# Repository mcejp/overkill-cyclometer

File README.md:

# Overkill Cyclocomputer

## Compile it

### For Pi Pico

Prerequisites:
- Raspberry Pi Pico SDK
- Recent arm-none-eabi-gcc toolchain
- ImageMagick (`convert` tool) & xxd

```
mkdir build
cd build
env PICO_SDK_PATH=... PICO_TOOLCHAIN_PATH=... cmake ..
make

# flash
cp bikECU.uf2 /media/RPI-RP2/
```

### For PC (Simulation)

Prerequisites:
- C++20 compiler
- Libretro frontent ([SDLArch](https://github.com/heuripedes/sdlarch) / [RetroArch](https://www.retroarch.com/))
- ImageMagick (`convert` tool) & xxd

```
mkdir build_libretro
cd build_libretro
cmake ..
make
sdlarch ./libbikECU_libretro.so
# alternatively:
# retroarch -L ./libbikECU_libretro.so
```

## Credits

- curses_vector fonts: http://www.bay12forums.com/smf/index.php?topic=161328.0
- libretro: Copyright (C) 2010-2020 The RetroArch team
- [SeeedGrayOLED library](https://github.com/Seeed-Studio/OLED_Display_96X96): Copyright (c) 2011 seeed technology inc.

## BOM

TBD

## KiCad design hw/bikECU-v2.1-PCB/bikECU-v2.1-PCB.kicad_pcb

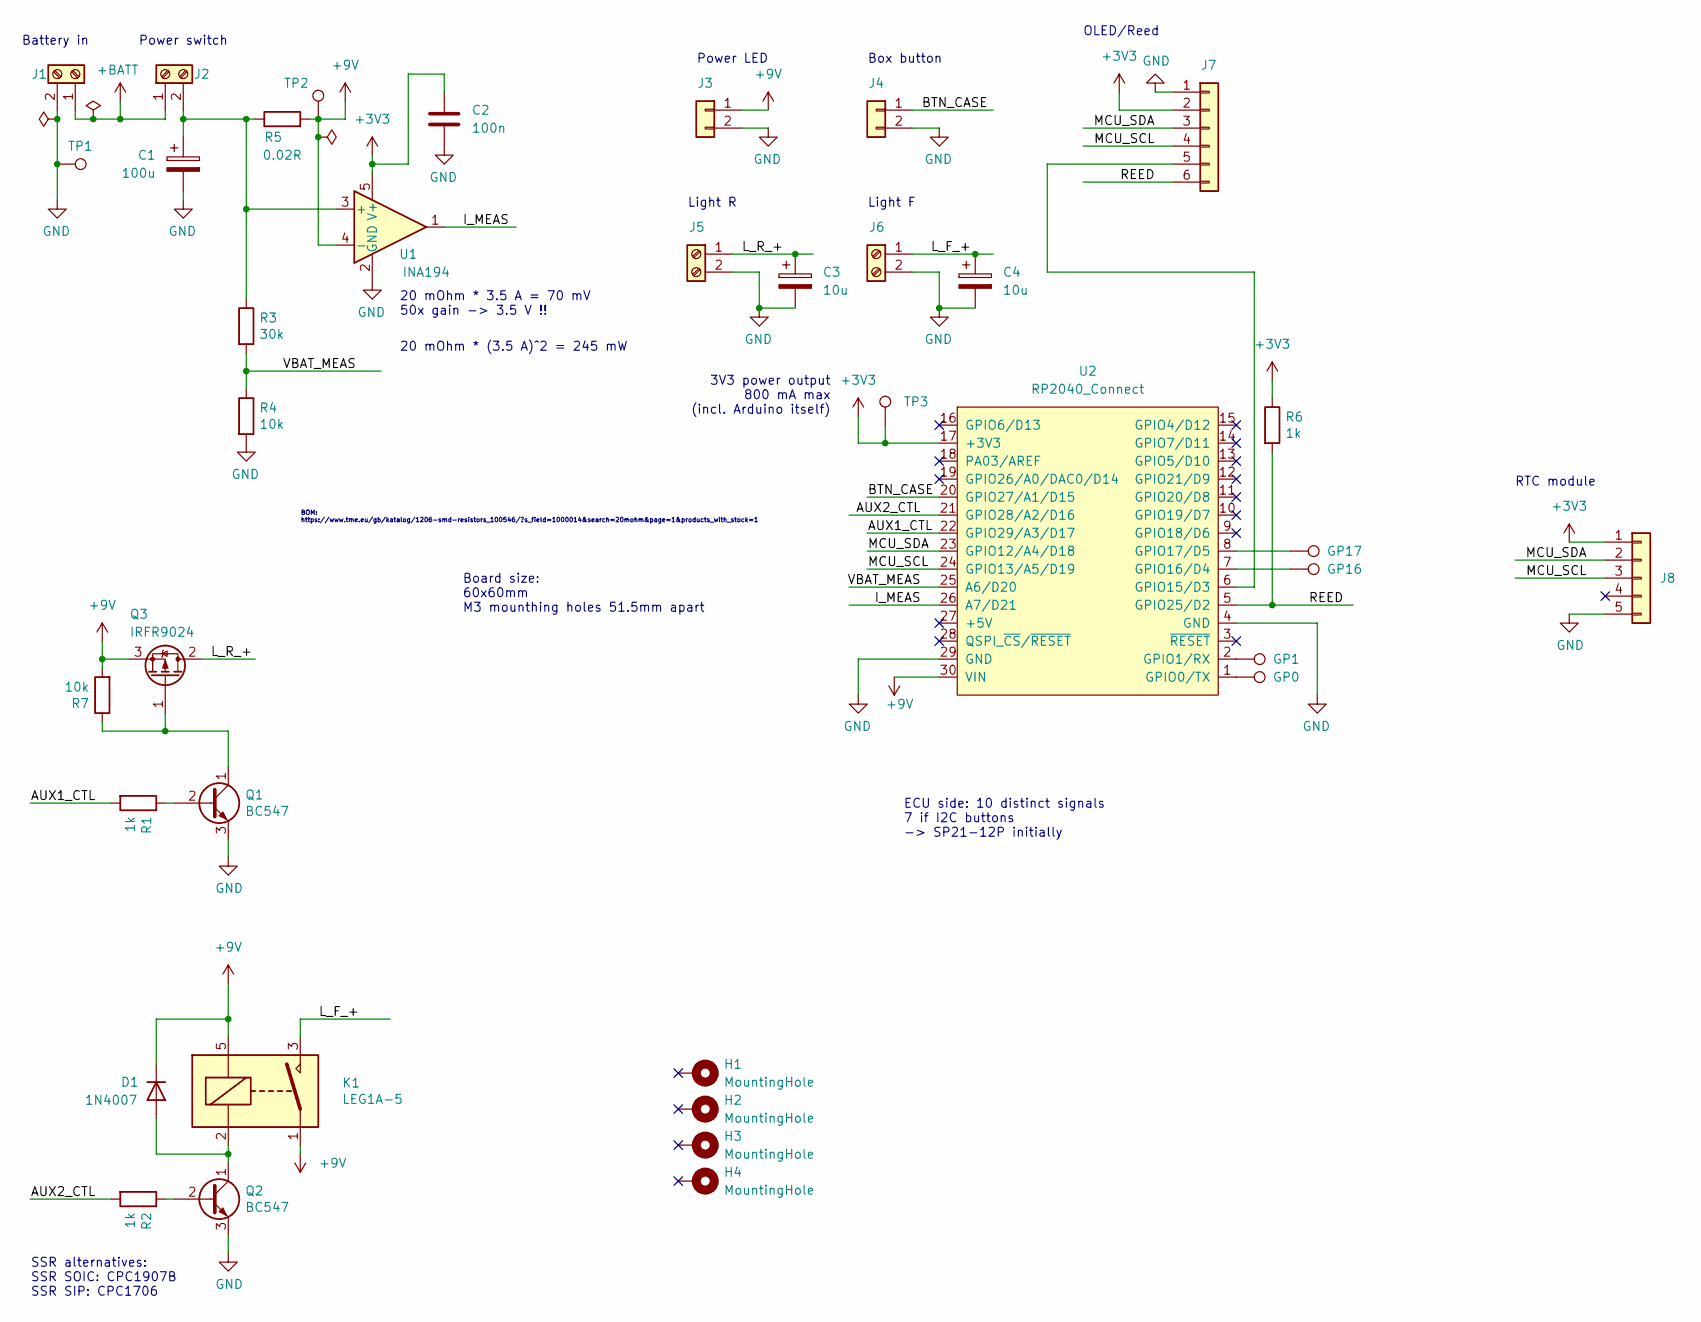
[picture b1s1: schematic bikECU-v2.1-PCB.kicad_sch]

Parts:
C1: 100u; CP_Radial_D6.3mm_P2.50mm
C2: 100n; C_0805_2012Metric_Pad1.18x1.45mm_HandSolder
C3, C4: 10u; CP_Radial_D5.0mm_P2.00mm
D1: 1N4007; D_DO-41_SOD81_P10.16mm_Horizontal
GP0, GP1, GP16, GP17: TestPoint; TestPoint_THTPad_D2.0mm_Drill1.0mm
H1, H2, H3, H4: MountingHole; MountingHole_3.2mm_M3_Pad
J1: Power_in; TerminalBlock_TE_282834-2_1x02_P2.54mm_Horizontal
J2: Power_sw; TerminalBlock_TE_282834-2_1x02_P2.54mm_Horizontal
J3: Power_led; JST_PH_B2B-PH-K_1x02_P2.00mm_Vertical
J4: Btn_box; JST_PH_B2B-PH-K_1x02_P2.00mm_Vertical
J5: Light_R; TerminalBlock_TE_282834-2_1x02_P2.54mm_Horizontal
J6: Light_F; TerminalBlock_TE_282834-2_1x02_P2.54mm_Horizontal
J7: Harness_conn; JST_PH_B6B-PH-K_1x06_P2.00mm_Vertical
J8: Rtc_hdr; PinHeader_1x05_P2.54mm_Vertical
K1: LEG1A-5; Relay_SPST_SANYOU_SRD_Series_Form_A
Q1, Q2: BC547; TO-92_Inline
Q3: IRFR9024; TO-252-2
R1, R2, R6: 1k; R_Axial_DIN0207_L6.3mm_D2.5mm_P10.16mm_Horizontal
R3: 30k; R_Axial_DIN0207_L6.3mm_D2.5mm_P10.16mm_Horizontal
R4, R7: 10k; R_Axial_DIN0207_L6.3mm_D2.5mm_P10.16mm_Horizontal
R5: 0.02R; R_1210_3225Metric_Pad1.30x2.65mm_HandSolder
TP1: GND; TestPoint_Pad_2.0x2.0mm
TP2: 9V; TestPoint_Pad_2.0x2.0mm
TP3: 3V3; TestPoint_Pad_2.0x2.0mm
U1: INA194; SOT-23-5_HandSoldering
U2: RP2040_Connect

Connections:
+3V3: C2.1, J7.2, J8.1, R6.1, TP3.1, U1.5 (V+), U2.17 (+3V3)
+9V: D1.1 (K), J3.1, K1.1, K1.5, Q3.3 (S), R5.2, R7.2, TP2.1, U1.4 (-), U2.30 (VIN)
+BATT: J1.1, J2.1
/AUX1_CTL: R1.2, U2.22 (GPIO29/A3/D17)
/AUX2_CTL: R2.2, U2.21 (GPIO28/A2/D16)
/BTN_CASE: J4.1, U2.20 (GPIO27/A1/D15)
/I_MEAS: U1.1, U2.26 (A7/D21)
/L_F_+: C4.1, J6.1, K1.3
/L_R_+: C3.1, J5.1, Q3.2 (D)
/MCU_SCL: J7.4, J8.3, U2.24 (GPIO13/A5/D19)
/MCU_SDA: J7.3, J8.2, U2.23 (GPIO12/A4/D18)
/REED: J7.6, R6.2, U2.5 (GPIO25/D2)
/VBAT_MEAS: R3.2, R4.1, U2.25 (A6/D20)
GND: C1.2, C2.2, C3.2, C4.2, J1.2, J3.2, J4.2, J5.2, J6.2, J7.1, J8.5, Q1.3 (E), Q2.3 (E), R4.2, TP1.1, U1.2 (GND), U2.4 (GND), U2.29 (GND)
unnamed: C1.1, J2.2, R3.1, R5.1, U1.3 (+)
unnamed: J7.5, U2.6 (GPIO15/D3)
unnamed: D1.2 (A), K1.2, Q2.1 (C)
unnamed: Q1.1 (C), Q3.1 (G), R7.1
unnamed: Q1.2 (B), R1.1
unnamed: Q2.2 (B), R2.1
unnamed: GP0.1, U2.1 (GPIO0/TX)
unnamed: GP1.1, U2.2 (GPIO1/RX)
unnamed: GP16.1, U2.7 (GPIO16/D4)
unnamed: GP17.1, U2.8 (GPIO17/D5)

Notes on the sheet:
20 mOhm * 3.5 A = 70 mV 50x gain -> 3.5 V !!
Power LED
BOM: https://www.tme.eu/gb/katalog/1206-smd-resistors_100546/?s_field=1000014&search=20mohm&page=1&products_with_stock=1
OLED/Reed
RTC module
Light F
Power switch
SSR alternatives: SSR SOIC: CPC1907B SSR SIP: CPC1706
Light R
Board size: 60x60mm M3 mounthing holes 51.5mm apart
Box button
Battery in
ECU side: 10 distinct signals 7 if I2C buttons -> SP21-12P initially
20 mOhm * (3.5 A)^2 = 245 mW
3V3 power output 800 mA max (incl. Arduino itself)

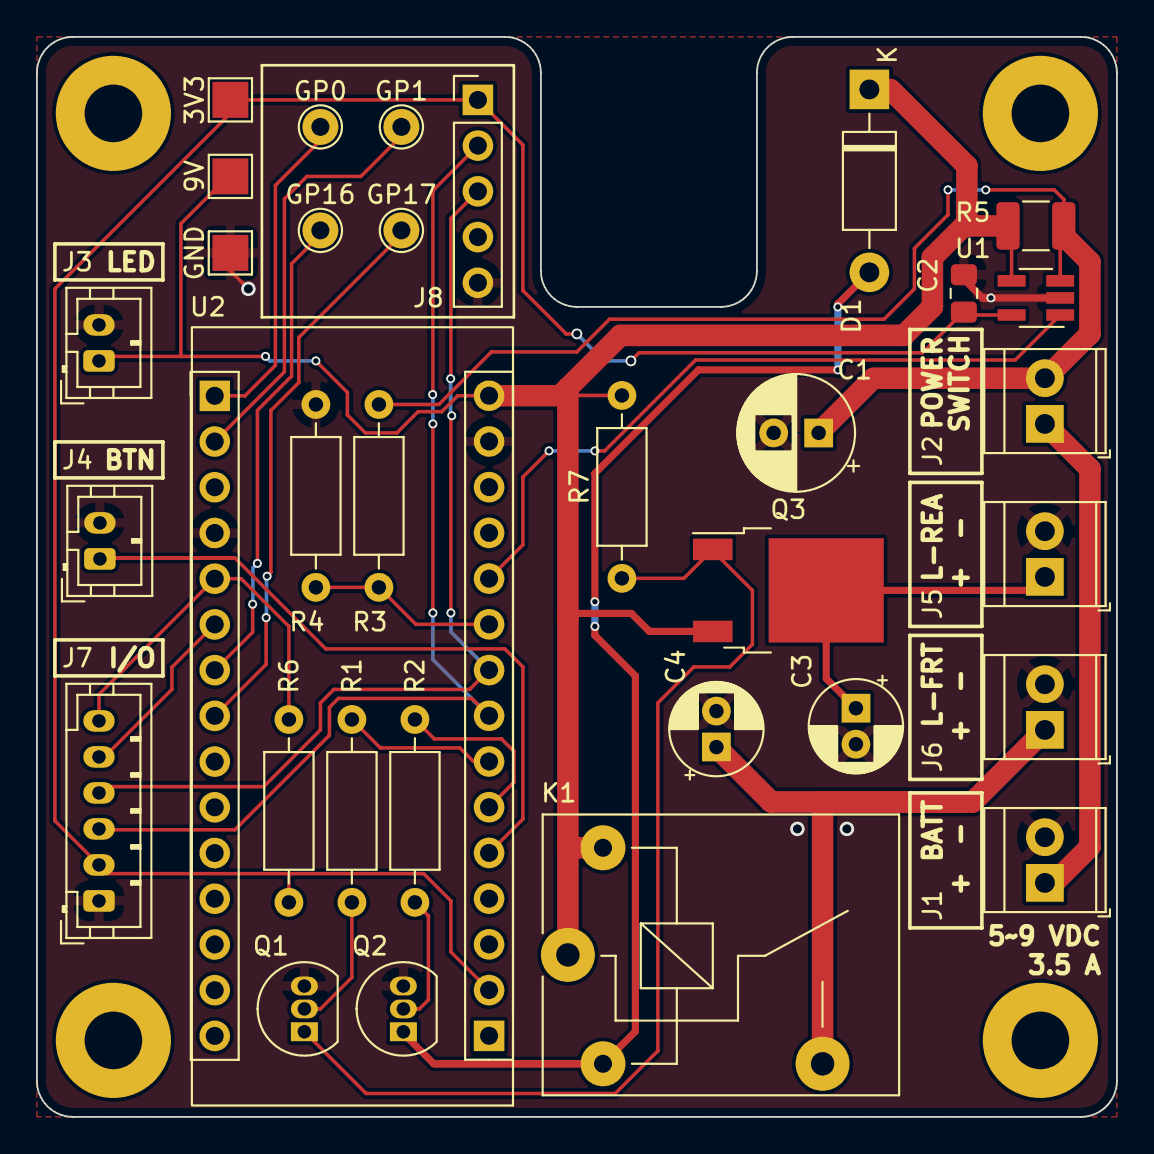
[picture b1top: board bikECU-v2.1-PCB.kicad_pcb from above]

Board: 2 copper layers, 60.0 x 60.0 mm, 37 parts (0 on the bottom side), 24 nets.

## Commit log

2021-10-14 Public release v1.0
2021-10-14 Replace incorrect datasheet
2021-10-14 Add OLED housing models
2021-10-15 Add connector datasheet
2021-11-24 Add EDAC 560 datasheet
2021-11-24 First iteration of sensor spacer
2021-11-25 Sensor spacer, take II
2021-12-12 Sensor spacer post-print adjustments
2021-12-12 Public release v1.1
2022-02-25 Add v2 ECU housing
2022-02-25 Add KiCad project for v2 system design
2022-05-11 Add pico_bootsel_via_double_reset
2022-05-11 Port to Arduino RP2040 Connect
2022-05-11 De-glitch sensor input
2022-05-11 libretro_main: Init rev_count with non-zero value
2022-05-11 Add v2.1 PCB design
2022-05-11 sw/doc: Add STORAGE.md
2022-07-31 Display splash image
2022-07-31 Dedicate multiple sectors to data logging
2022-08-05 Add Devprop over USB (not beautiful, but works)
2022-08-07 Implement DS3231 and its properties
2023-05-27 Display V_bat reading
2023-05-29 Show a clock + alternate between V_bat and ambient temperature
2023-05-29 Add timestamps to logged data
2024-11-07 Move SH1107_datasheet.pdf
2024-11-17 Enable AUX output (used for front light)
